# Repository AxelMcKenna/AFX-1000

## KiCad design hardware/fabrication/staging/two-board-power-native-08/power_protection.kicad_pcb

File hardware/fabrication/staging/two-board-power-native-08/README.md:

# TBP08: module-input branch and return-star candidate

The combined power schematic now includes a dedicated feed for both TMR 1-1215
modules and a separate primary force return through a copper net tie.
**This branch is not accepted for fabrication:** fault review identified a
post-short output-undervoltage condition that requires a different cutoff
strategy. The complete two-board unit remains unfinished.

Open [power_protection.kicad_pro](power_protection.kicad_pro).

| Native check | Result |
| --- | --- |
| Electrical parts / schematic pin entries | 1,090 / 3,413 |
| Footprints, including 15 mechanical | 1,105 |
| Physical pad instances mapped | 3,478 |
| Native geometry / schematic-parity findings | 0 / 0 |
| ERC | 0 errors; 2 retained floating-reference warnings |
| Open connections | **2,707** |
| Original parts / full footprint geometries preserved | 1,077 / 1,092 |

## Circuit captured

P_U101.17/.18 and P_C103.1 supply G_U1, a TPS259474LRPWR eFuse. Its output feeds
N_U17.2, N_U22.2 and the existing module input filters. This supply is available
before NF GLOBAL_MASTER; no final-enable dependency is introduced. The 13 new
parts comprise the eFuse, five resistors, four capacitors, two clamps and one
copper net tie. No physical part from TBP06 is removed or changed. The former
external-input power flag is removed because G_U1 now supplies that net.

G_NT1 joins PWR_MODULE_INPUT_GND to PWR_AGND. Its system-ground end must return
at P_C103.2. It is the only declared primary-return connection; there is no
local NF quiet-ground tie. The star currently sits near the bulk capacitor as
an **unrouted placement placeholder**. The new cell is also provisionally placed,
well away from its final electrically optimized location. Neither placement
establishes current-loop, ground-drop, thermal or housing acceptance.

The [independent audit](module-feed-audit.json) checks every new pin, preserves
the original complete pin partition and all 1,092 prior footprint geometries,
maps all physical pads, and rejects seven incorrect wiring variants. It also
rechecks the earlier 32 fault/reset cases, two source-sense channels and 64
settled UV-fault cases. The RPW footprint matches the reviewed manufacturer's
copper dimensions and stencil example; process acceptance remains open.

TBP07's first native check found nine new-cell spacing errors, three Datasheet
field mismatches and 46 schematic-grid warnings. TBP08 corrects those findings
without suppressing any check. [Native results](review.json) are independently
bound to the actual checked files.

## Electrical screens and unresolved fault

With a declared total resistance budget of 0.5% and the specified threshold and
input-leakage limits, the input branch enables at 10.466–11.111 V, disables on
falling input at 9.515–10.143 V and disables on rising input at 13.879–14.710 V.
These are conditional on the passive budget and local reference. The proposed
12 V ±5% supply window and 0.10 V branch-distribution allowance still need
acceptance against the complete supply and layout.

The nominal current limit is 0.514 A. Scaling the manufacturer's 6.65 kΩ test
row to the chosen 6.49 kΩ produces a 0.433–0.592 A **model screen**, not a new
guaranteed test row. The nominal output ramp is 28.2 ms to 12 V. A 0.35 A total
load and 60 µF total output capacitance fit a conditional charging-current
screen, but the modules' startup/internal capacitance and minimum efficiency
are not bounded by the available table. Exact passive order codes, effective
capacitance, surge behavior and per-module fault containment remain open.

Most importantly, the selected eFuse does not latch immediately on every short.
After fast trip it can restart in current limit. The audit records a hypothetical
12 V input / 8.7 V output case whose typical thermal model does not reach thermal
shutdown. Input undervoltage sensing cannot detect that output sag. This is an
identified protection gap, not evidence that a real unit was tested or failed.
The [cutoff review](../two-board-module-cutoff-review-01/README.md) identifies
TPS26601 in its timer-operated latch-off mode as the next candidate. It has not
yet replaced G_U1; its pin map, return reference, current/slew settings, land
pattern and circuit must be implemented and checked.

## Remaining work

Resolve the module cutoff and receiving limits, then complete loaded AUX,
reference/sense/clamp, high-temperature logic and deep-UV/minimum-OFF reviews.
Optimize critical power placement and route both boards; finish the signal/power
interface and ESS codec land pattern. Complete the manufacturing BOM/stack/
process and fabrication files, full installed-fit/support/cooling checks and
prototype inspection/bring-up plan. Prototype measurements belong in that plan;
they are not represented as measurements of an unbuilt unit.

The [native module-sheet SVG](plots-module/G_module_input.svg) was inspected.
Its long G_NT1 pin names overlap and should be shortened in the next circuit
revision. The hierarchy-cover export in `plots/schematic/` is not the module
sheet; the direct export linked here is the correct visual reference.

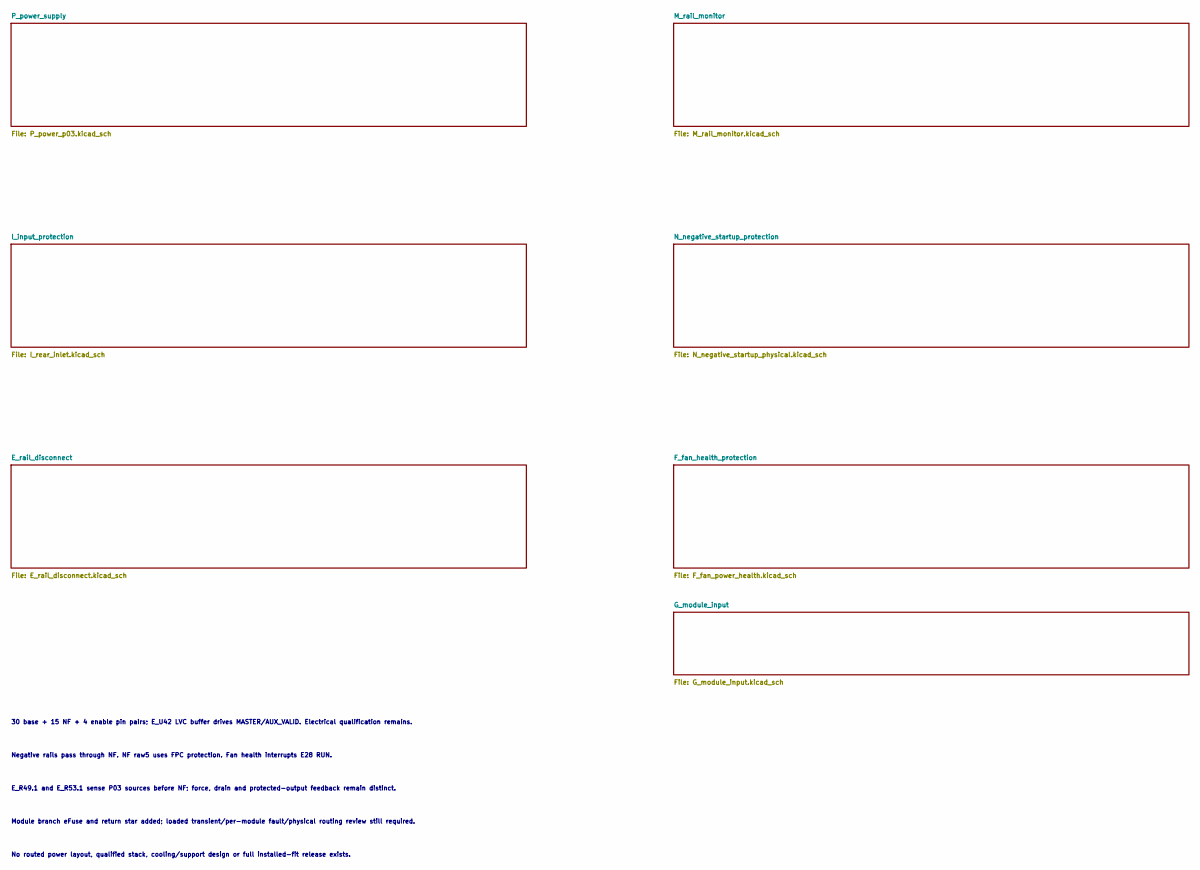
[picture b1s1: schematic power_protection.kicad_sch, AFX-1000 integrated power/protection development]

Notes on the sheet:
30 base + 15 NF + 4 enable pin pairs; E_U42 LVC buffer drives MASTER/AUX_VALID. Electrical qualification remains.
Negative rails pass through NF. NF raw5 uses FPC protection. Fan health interrupts E28 RUN.
E_R49.1 and E_R53.1 sense P03 sources before NF; force, drain and protected-output feedback remain distinct.
Module branch eFuse and return star added; loaded transient/per-module fault/physical routing review still required.
No routed power layout, qualified stack, cooling/support design or full installed-fit release exists.

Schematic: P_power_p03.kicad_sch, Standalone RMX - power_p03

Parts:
P_C1, P_C63: 10uF 63V X7R; C_1210_3225Metric
P_C2, P_C3, P_C5, P_C6, P_C8, P_C9, P_C37, P_C42, P_C52, P_C57, P_C64, P_C65, P_C67, P_C68, P_C70, P_C204, P_C205, P_C224, P_C225, P_C254: 22uF 50V X7R 20% TDK C3225X7R1H226M250AC; C_1210_3225Metric
P_C4, P_C7, P_C10, P_C35, P_C38, P_C40, P_C43, P_C50, P_C53, P_C55, P_C58, P_C59, P_C61, P_C66, P_C69, P_C71: 100nF 50V X7R; C_0805_2012Metric
P_C11, P_C30, P_C107, P_C108: 100nF 16V X7R; C_0805_2012Metric
P_C12, P_C14, P_C73, P_C75: 68pF 50V C0G 5%; C_0805_2012Metric
P_C13, P_C15, P_C74, P_C76: 330nF 16V X7R; C_0805_2012Metric
P_C31: 2.2uF 16V X7R; C_0805_2012Metric
P_C32, P_C33: 1uF film 63V 10% MKS2C041001F00KSSD; C_Rect_L7.2mm_W5.0mm_P5.00mm
P_C34, P_C39, P_C49, P_C54, P_C240: 47nF 50V C0G 5%; C_1210_3225Metric
P_C36, P_C41, P_C51, P_C56: 10uF 50V X7R; C_1210_3225Metric
P_C60, P_C62, P_C105: 1uF 50V X7R; C_0805_2012Metric
P_C72, P_C210, P_C211, P_C230, P_C231: 100nF 50V X7R 10% TDK C1005X7R1H104K050BB; C_0402_1005Metric
P_C101, P_C102: 2.2uF 100V X7R; C_1210_3225Metric
P_C103: 220uF 35V electrolytic 20% (EEUFR1V221); CP_Radial_D8.0mm_P3.50mm
P_C104: 1uF 50V X7R; C_1210_3225Metric
P_C106: 10uF 25V X7R 10% TDK C3225X7R1E106K250AC; C_1210_3225Metric
P_C109: 1nF 16V C0G 5%; C_0805_2012Metric
P_C110: 10nF 25V C0G 5% KEMET C0603C103J3GACTU; C_0603_1608Metric
P_C113: 1uF 100V X7S 10% TDK C2012X7S2A105K125AE; C_0805_2012Metric
P_C200, P_C220: 4.7uF 25V X7R 10% TDK C2012X7R1E475K125AB; C_0805_2012Metric
P_C201, P_C221, P_C255, P_C301, P_C302: 100nF 50V X7R; C_0603_1608Metric
P_C202, P_C203, P_C222, P_C223: 2.2uF 50V X7R 10% TDK C2012X7R1H225K125AC; C_0805_2012Metric
P_C206, P_C207, P_C208, P_C209, P_C226, P_C227, P_C228, P_C229: 47uF 25V X7S 20% TDK C3225X7S1E476M250AC; C_1210_3225Metric
P_C241: 1uF 25V X7R; C_1210_3225Metric
P_C242, P_C243, P_C244, P_C245, P_C246, P_C247, P_C248, P_C249, P_C250, P_C251: 100nF 25V C0G 5% KEMET C1206C104J3GACTU; C_1206_3216Metric
P_C252, P_C253: 1uF 16V X7R; C_1210_3225Metric
P_C300: 10nF 50V C0G 5%; C_0805_2012Metric
P_C401, P_C402: 100nF 50V X7R C0603C104K5RACTU; C0603
P_C403: 10nF 50V C0G C0603C103J5GACTU; C0603
P_D1, P_D2, P_D3, P_D4, P_D103: SS16-E3/61T; D_SMA
P_D101: SMBJ33CA-E3/52; D_SMB
P_D102: BAS116,215; SOT-23
P_J2: Header6; PinHeader_1x06_P2.54mm_Vertical
P_J3: Header2; PinHeader_1x02_P2.54mm_Vertical
P_J20, P_J21, P_J23, P_J24: Wurth 7466003R M3 SMT; Wurth_7466003R
P_J22: P03 READY test; PinHeader_1x03_P2.54mm_Vertical
P_J103: Bare POWER_READY probe pads, no fitted header; Probe2_P2.54_D1
P_J104: JST B3B-XH-A (XHP-3/SXH-001T-P0.6); JST_XH_B3B-XH-A_1x03_P2.50mm_Vertical
P_J106: JST B4B-XH-A (XHP-4/SXH-001T-P0.6); JST_XH_B4B-XH-A_1x04_P2.50mm_Vertical
P_L1, P_L6: 33uH 20% SRP7050WA-330M; SRP7050WA
P_L2, P_L3, P_L7, P_L8: 68uH 20% SRP1050WA-680M; SRP1050WA
P_L20, P_L23: 4.7uH 20% Coilcraft XAL7030-472MEC; L_Coilcraft_XAL7030-472
P_Q101: PSMN012-100YL,115; LFPAK56
P_Q102: BSS138-7-F; SOT-23
P_Q103: DMN2056U-7; SOT-23
P_R1: 300k 0.01% 5ppm; R_0805_2012Metric
P_R2, P_R3, P_R4, P_R45, P_R46: 15k 0.01% 5ppm; R_0805_2012Metric
P_R5, P_R20, P_R21, P_R34, P_R35: 330k 0.01% 5ppm; R_0805_2012Metric
P_R6, P_R7, P_R49, P_R50: 4.7k 1%; R_0805_2012Metric
P_R17, P_R19, P_R110: 1k 1%; R_0805_2012Metric
P_R18, P_R120: 100k 1%; R_0805_2012Metric
P_R22, P_R27, P_R36, P_R41, P_R243, P_R244: 100k 0.01% 5ppm; R_0805_2012Metric
P_R23, P_R28, P_R37, P_R42, P_R241: 6.8k 1%; R_0805_2012Metric
P_R24, P_R38: 9.09k 1%; R_0805_2012Metric
P_R25, P_R39, P_R47, P_R306: 200k 0.01% 5ppm; R_0805_2012Metric
P_R26, P_R40, P_R308: 180k 0.01% 5ppm; R_0805_2012Metric
P_R29, P_R43: 5.62k 1%; R_0805_2012Metric
P_R44: 240k 0.01% 5ppm; R_0805_2012Metric
P_R48, P_R301, P_R303, P_R305, P_R307, P_R309, P_R314: 10k 0.01% 5ppm; R_0805_2012Metric
P_R101, P_R103, P_R117: 309k 0.1% 10ppm; R_0805_2012Metric
P_R102: 40.2k 0.1% 10ppm; R_0805_2012Metric
P_R104: 28k 0.1% 10ppm; R_0805_2012Metric
P_R105: 68.1k 0.1% 10ppm; R_0805_2012Metric
P_R106, P_R109, P_R118, P_R119: 10k 0.1% 10ppm; R_0805_2012Metric
P_R107: 4.02k 0.1% 10ppm; R_0805_2012Metric
P_R108: 11.7k 0.1% 10ppm; R_0805_2012Metric
P_R111, P_R204, P_R224, P_R246: 10k 1%; R_0805_2012Metric
P_R112, P_R114: 47k 1%; R_0805_2012Metric
P_R113: 3.3k 1%; R_0805_2012Metric
P_R115: 30.9k 0.1% 10ppm; R_0805_2012Metric
P_R116: 3.09k 0.1% 10ppm; R_0805_2012Metric
P_R121: 100 1%; R_0805_2012Metric
P_R130: 49.9 0.01% 5ppm; R_0805_2012Metric
P_R200: 9k 0.01% 2ppm Susumu RG2012L-902-L-T1; R_0805_2012Metric
P_R201: 1k 0.01% 2ppm Susumu RG2012L-102-L-T1; R_0805_2012Metric
P_R202, P_R222: 24.3k 1%; R_0805_2012Metric
P_R203, P_R223: 18.2k 0.1% 25ppm Panasonic ERA6AEB1822V; R_0805_2012Metric
P_R205, P_R225: 22k 1%; R_0805_2012Metric
P_R206: 54.9 0.1% 25ppm Panasonic ERA6AEB549V; R_0805_2012Metric
P_R220: 11k 0.01% 5ppm; R_0805_2012Metric
P_R221, P_R311: 1k 0.01% 5ppm; R_0805_2012Metric
P_R240: 100 0.01% 5ppm; R_0805_2012Metric
P_R242: 120 0.01% 5ppm; R_0805_2012Metric
P_R245: 2.21k 1%; R_0805_2012Metric
P_R300, P_R302: 87.6k 0.01% 5ppm; R_0805_2012Metric
P_R304: 324k 0.01% 5ppm; R_0805_2012Metric
P_R310: 590 0.01% 5ppm; R_0805_2012Metric
P_R312: 7.5k 0.01% 5ppm; R_0805_2012Metric
P_R313: 1M 0.01% 5ppm; R_0805_2012Metric
P_R315: 750k 0.01% 5ppm; R_0805_2012Metric
P_R316: 2.2k 0.1% 25ppm Panasonic ERA6AEB222V; R_0805_2012Metric
P_R401: 100k ohm TNPW0805100KBEEA; R0805
P_R402: 10M 1% CRCW080510M0FKEA; R0805
P_R403: 1k 1% CRCW12061K00FKEA; R1206
P_U1, P_U13: LT3471EDD#PBF; DFN-10-1EP_3x3mm_P0.5mm_EP1.65x2.38mm
P_U4: REF5025EIDR; SOIC-8_3.9x4.9mm_P1.27mm
P_U5: OPA4192ID; SOIC-14_3.9x8.7mm_P1.27mm
P_U6, P_U24: OPA2192ID; SOIC-8_3.9x4.9mm_P1.27mm
P_U7: LT3080IMS8E#PBF; MSOP-8-1EP_3x3mm_P0.65mm_EP1.68x1.88mm
P_U8: LT3080IQ#PBF; TO-263-5_TabPin3
P_U10, P_U11: LT3090IDD#PBF; DFN-10-1EP_3x3mm_P0.5mm_EP1.65x2.38mm
P_U12: LT1634AIS8-2.5#PBF; SOIC-8_3.9x4.9mm_P1.27mm
P_U20, P_U23: TPS543620RPYR; TPS543620_RPY0014A
P_U21: ADR4550BRZ; SOIC-8_3.9x4.9mm_P1.27mm
P_U22: LT3045IDD#PBF; DFN-10-1EP_3x3mm_P0.5mm_EP1.65x2.38mm
P_U25: LTC2910HGN#PBF; SSOP-16_3.9x4.9mm_P0.635mm
P_U26: SN74LVC1G97DBVR; SOT-23-6
P_U101: TPS26630RGER; Texas_RGE0024H_VQFN-24-1EP_4x4mm_P0.5mm_EP2.7x2.7mm
P_U102: TPS7A1601DGNR; MSOP-8-1EP_3x3mm_P0.65mm_EP1.68x1.88mm
P_U103: TLV7011DBVR; SOT-23-5
P_U201: TPS389001DSET; TI_DSE0006A
P_U202: SN74AUP1G17DCKR; TI_DCK0005A

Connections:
/P_power_supply/AUX_FB: P_R109.1, P_R130.2, P_U102.2 (FB)
/P_power_supply/AUX_START_DELAY: P_C110.1 (+), P_U102.7 (DELAY)
/P_power_supply/AX03_RUN_DRIVE: P_R403.1, P_U202.4 (Y)
/P_power_supply/AX03_SOURCE_CT: P_C403.1, P_U201.5 (CT)
/P_power_supply/AX03_SOURCE_RESET: P_R401.2, P_R402.1, P_U201.6 (RESET_N), P_U202.2 (A)
/P_power_supply/BLOCK_DRV: P_Q102.1 (GATE), P_U101.4 (DRV)
/P_power_supply/BLOCK_GATE: P_Q101.4 (GATE), P_Q102.3 (DRAIN), P_U101.3 (B_GATE)
/P_power_supply/CUK_NODE: P_C1.2, P_D2.2 (A), P_L3.1
/P_power_supply/FAST_OV_GATE: P_Q103.1 (GATE), P_R120.1, P_R121.2
/P_power_supply/FAST_OV_OUT: P_R117.1, P_R121.1, P_U103.1 (OUT)
/P_power_supply/FAST_OV_REF: P_C109.1 (+), P_R118.2, P_R119.1, P_U103.4 (IN-)
/P_power_supply/FAST_OV_SENSE: P_R115.2, P_R116.1, P_R117.2, P_U103.3 (IN+)
/P_power_supply/INPUT_ILIM: P_R107.1, P_U101.10 (ILIM)
/P_power_supply/INPUT_OV: P_D102.1 (ANODE), P_R103.2, P_R104.1, P_U101.7 (OVP)
/P_power_supply/INPUT_PGTH: P_R105.2, P_R106.1, P_U101.15 (PGTH)
/P_power_supply/INPUT_SLEW: P_C105.1 (+), P_U101.9 (dVdT)
/P_power_supply/INPUT_UV: P_R101.2, P_R102.1, P_U101.6 (UVLO)
/P_power_supply/LO_CUK_NODE: P_C63.2, P_D4.2 (A), P_L8.1
/P_power_supply/LO_N_FB: P_C75.2, P_R46.2, P_R47.1, P_U13.4 (FB2P)
/P_power_supply/LO_N_RMID: P_R47.2, P_R48.1
/P_power_supply/LO_N_SS: P_C76.1, P_R50.2, P_U13.7 (SHDN_SS2)
/P_power_supply/LO_N_SW: P_C63.1, P_L7.2, P_U13.6 (SW2)
/P_power_supply/LO_P_FB: P_C73.2, P_R44.2, P_R45.1, P_U13.1 (FB1N)
/P_power_supply/LO_P_SS: P_C74.1, P_R49.2, P_U13.9 (SHDN_SS1)
/P_power_supply/LO_P_SW: P_D3.2 (A), P_L6.2, P_U13.10 (SW1)
/P_power_supply/LO_REF_1V: P_C72.1, P_R46.1, P_U13.2 (FB1P), P_U13.3 (VREF)
/P_power_supply/N12_DRIVE: P_C54.1, P_R42.1, P_U6.7 (OUT)
/P_power_supply/N12_FB: P_C54.2, P_R40.2, P_R41.1, P_U6.6 (-)
/P_power_supply/N12_RMID: P_R39.2, P_R40.1
/P_power_supply/N12_SET: P_C55.1, P_R39.1, P_R42.2, P_U11.4 (SET)
/P_power_supply/N19_DRIVE: P_C49.1, P_R37.1, P_U6.1 (OUT)
/P_power_supply/N19_FB: P_C49.2, P_R35.2, P_R36.1, P_U6.2 (-)
/P_power_supply/N19_RMID: P_R34.2, P_R35.1
/P_power_supply/N19_SET: P_C50.1, P_R34.1, P_R37.2, P_U10.4 (SET)
/P_power_supply/NREF_2V5: P_R18.1, P_R19.1, P_U12.4 (GND/ANODE), P_U12.5 (TEST)
/P_power_supply/NREF_FILTER: P_C33.1, P_R19.2, P_U6.3 (+), P_U6.5 (+)
/P_power_supply/P03_ANA_DIV: P_R242.2, P_R243.1, P_R244.1
/P_power_supply/P03_ANA_DRIVE: P_C240.1 (+), P_R241.1, P_U24.1 (OUT_A)
/P_power_supply/P03_ANA_FB: P_C240.2 (-), P_R244.2, P_U24.2 (IN_A_N)
/P_power_supply/P03_ANA_SET: P_C241.1 (+), P_R241.2, P_R242.1, P_U22.7 (SET)
/P_power_supply/P03_AUX_TRIM: P_R108.2, P_R130.1
/P_power_supply/P03_A_BOOT: P_C221.1 (+), P_U23.14 (BOOT)
/P_power_supply/P03_A_BP5: P_C220.1 (+), P_U23.6 (BP5)
/P_power_supply/P03_A_ENABLE: P_R224.2, P_R225.1, P_U23.7 (EN)
/P_power_supply/P03_A_FB: P_R220.2, P_R221.1, P_U23.4 (FB)
/P_power_supply/P03_A_FSEL: P_R222.1, P_U23.1 (SYNC_FSEL)
/P_power_supply/P03_A_MODE: P_R223.1, P_U23.2 (MODE)
/P_power_supply/P03_A_SW: P_C221.2 (-), P_L23.1 (SW), P_U23.10 (SW), P_U23.13 (SW_BOOT_RETURN)
/P_power_supply/P03_D_BOOT: P_C201.1 (+), P_U20.14 (BOOT)
/P_power_supply/P03_D_BP5: P_C200.1 (+), P_U20.6 (BP5)
/P_power_supply/P03_D_ENABLE: P_R204.2, P_R205.1, P_U20.7 (EN)
/P_power_supply/P03_D_FB: P_R201.1, P_R206.2, P_U20.4 (FB)
/P_power_supply/P03_D_FB_TRIM: P_R200.2, P_R206.1
/P_power_supply/P03_D_FSEL: P_R202.1, P_U20.1 (SYNC_FSEL)
/P_power_supply/P03_D_MODE: P_R203.1, P_U20.2 (MODE)
/P_power_supply/P03_D_SW: P_C201.2 (-), P_L20.1 (SW), P_U20.10 (SW), P_U20.13 (SW_BOOT_RETURN)
/P_power_supply/P03_MON_ANA: P_R302.2, P_R303.1, P_U25.2 (V2)
/P_power_supply/P03_MON_BUCK_OK: P_U25.5 (V5), P_U26.4 (Y)
/P_power_supply/P03_MON_DIG: P_R300.2, P_R301.1, P_U25.1 (V1)
/P_power_supply/P03_MON_N12: P_R314.2, P_R315.1, P_U25.8 (V8)
/P_power_supply/P03_MON_N19: P_R312.2, P_R313.1, P_U25.7 (V7)
/P_power_supply/P03_MON_NEG_BIAS: P_R310.2, P_R311.1, P_R312.1, P_R314.1
/P_power_supply/P03_MON_P12: P_R306.2, P_R307.1, P_U25.4 (V4)
/P_power_supply/P03_MON_P19: P_R304.2, P_R305.1, P_U25.3 (V3)
/P_power_supply/P03_MON_REF: P_R310.1, P_U25.10 (REF)
/P_power_supply/P03_MON_TIMER: P_C300.1 (+), P_U25.15 (TMR)
/P_power_supply/P03_MON_VIN: P_R308.2, P_R309.1, P_U25.6 (V6)
/P_power_supply/P03_PRE6V: P_C226.1 (+), P_C227.1 (+), P_C228.1 (+), P_C229.1 (+), P_C253.1 (+), P_L23.2 (OUT), P_R220.1, P_U21.2 (VIN), P_U22.1 (IN), P_U22.2 (IN), P_U22.3 (EN_UV), P_U22.6 (PGFB)
/P_power_supply/P03_REF5: P_C252.1 (+), P_R240.1, P_U21.6 (VOUT)
/P_power_supply/P03_REF_FILTER: P_C242.1 (+), P_C243.1 (+), P_C244.1 (+), P_C245.1 (+), P_C246.1 (+), P_C247.1 (+), P_C248.1 (+), P_C249.1 (+), P_C250.1 (+), P_C251.1 (+), P_R240.2, P_U24.3 (IN_A_P)
/P_power_supply/P03_SOURCES_READY: P_R246.2, P_U20.3 (PGOOD), P_U23.3 (PGOOD), P_U26.3 (In0)
/P_power_supply/P03_SPARE_24: P_U24.6 (IN_B_N), P_U24.7 (OUT_B)
/P_power_supply/P03_SPARE_C: P_U5.8 (OUT), P_U5.9 (-)
/P_power_supply/P12_DRIVE: P_C39.1, P_R28.1, P_U5.7 (OUT)
/P_power_supply/P12_FB: P_C39.2, P_R26.2, P_R27.1, P_U5.6 (-)
/P_power_supply/P12_RMID: P_R25.2, P_R26.1
/P_power_supply/P12_SET: P_C40.1, P_R25.1, P_R28.2, P_U8.2 (SET)
/P_power_supply/P19_DRIVE: P_C34.1, P_R23.1, P_U5.1 (OUT)
/P_power_supply/P19_FB: P_C34.2, P_R21.2, P_R22.1, P_U5.2 (-)
/P_power_supply/P19_RMID: P_R20.2, P_R21.1
/P_power_supply/P19_SET: P_C35.1, P_R20.1, P_R23.2, P_U7.4 (SET)
/P_power_supply/POWER_READY: P_J22.3 (POWER_READY), P_J103.2 (POWER_READY), P_R110.2, P_R204.1, P_R224.1, P_U26.6 (In2), P_U101.16 (PGOOD)
/P_power_supply/PREF_2V5: P_C31.1, P_R17.1, P_U4.6 (VOUT)
/P_power_supply/PREF_FILTER: P_C32.1, P_R17.2, P_U5.3 (+), P_U5.5 (+)
/P_power_supply/RAW_N17: P_C56.1, P_C67.1, P_C68.1, P_C69.1, P_C75.1, P_L8.2, P_R48.2, P_U11.8 (ILIM), P_U11.9 (IN), P_U11.10 (IN), P_U11.11 (EP/IN)
/P_power_supply/RAW_N22: P_C8.1, P_C9.1, P_C10.1, P_C14.1, P_C51.1, P_C61.1, P_C62.1, P_L3.2, P_R5.2, P_R18.2, P_U6.4 (V-), P_U10.8 (ILIM), P_U10.9 (IN), P_U10.10 (IN), P_U10.11 (EP/IN)
/P_power_supply/RAW_N_FB: P_C14.2, P_R4.2, P_R5.1, P_U1.4 (FB2P)
/P_power_supply/RAW_N_SS: P_C15.1, P_R7.2, P_U1.7 (SHDN_SS2)
/P_power_supply/RAW_N_SW: P_C1.1, P_L2.2, P_U1.6 (SW2)
/P_power_supply/RAW_P17: P_C41.1, P_C64.1, P_C65.1, P_C66.1, P_C73.1, P_D3.1 (K), P_R44.1, P_U8.4 (VCONTROL), P_U8.5 (IN)
/P_power_supply/RAW_P22: P_C5.1, P_C6.1, P_C7.1, P_C12.1, P_C36.1, P_C59.1, P_C60.1, P_D1.1 (K), P_R1.1, P_U5.4 (V+), P_U7.5 (VCONTROL), P_U7.7 (IN), P_U7.8 (IN)
/P_power_supply/RAW_P_FB: P_C12.2, P_R2.2, P_R3.1, P_U1.1 (FB1N)
/P_power_supply/RAW_P_RMID: P_R1.2, P_R2.1
/P_power_supply/RAW_P_SS: P_C13.1, P_R6.2, P_U1.9 (SHDN_SS1)
/P_power_supply/RAW_P_SW: P_D1.2 (A), P_L1.2, P_U1.10 (SW1)
/P_power_supply/SPARE_OUT: P_U5.13 (SPARE-), P_U5.14 (SPARE_OUT)
/P_power_supply/SW_REF_1V: P_C11.1, P_R4.1, P_U1.2 (FB1P), P_U1.3 (VREF)
/P_power_supply/VIN_IC: P_C102.1 (+), P_C113.1 (+), P_Q101.5 (DRAIN/MB), P_R115.1, P_U101.1 (IN), P_U101.2 (IN), P_U102.5 (EN), P_U102.8 (IN)
PWR_5V_DIG_SRC: P_C30.1, P_C206.1 (+), P_C207.1 (+), P_C208.1 (+), P_C209.1 (+), P_J3.1 (5V_DIG), P_J23.1, P_L20.2 (OUT), P_R6.1, P_R7.1, P_R49.1, P_R50.1, P_R200.1, P_R300.1, P_U4.1 (EN), P_U4.2 (VIN), P_U10.5 (SHDN), P_U11.5 (SHDN); also elsewhere on the board
PWR_AGND: P_C2.2, P_C3.2, P_C4.2, P_C5.2, P_C6.2, P_C7.2, P_C8.2, P_C9.2, P_C10.2, P_C11.2, P_C13.2, P_C15.2, P_C30.2, P_C31.2, P_C32.2, P_C33.2, P_C35.2, P_C36.2, P_C37.2, P_C38.2, P_C40.2, P_C41.2, P_C42.2, P_C43.2, P_C50.2, P_C51.2, P_C52.2, P_C53.2, P_C55.2, P_C56.2, P_C57.2, P_C58.2, P_C59.2, P_C60.2, P_C61.2, P_C62.2, P_C64.2, P_C65.2, P_C66.2, P_C67.2, P_C68.2, P_C69.2, P_C70.2, P_C71.2, P_C72.2, P_C74.2, P_C76.2, P_C101.2 (-), P_C102.2 (-), P_C103.2 (-), P_C104.2 (-), P_C105.2 (-), P_C106.2 (-), P_C107.2 (-), P_C108.2 (-), P_C109.2 (-), P_C110.2 (-), P_C113.2 (-), P_C200.2 (-), P_C202.2 (-), P_C203.2 (-), P_C204.2 (-), P_C205.2 (-), P_C206.2 (-), P_C207.2 (-), P_C208.2 (-), P_C209.2 (-), P_C210.2 (-), P_C211.2 (-), P_C220.2 (-), P_C222.2 (-), P_C223.2 (-), P_C224.2 (-), P_C225.2 (-), P_C226.2 (-), P_C227.2 (-), P_C228.2 (-), P_C229.2 (-), P_C230.2 (-), P_C231.2 (-), P_C241.2 (-), P_C242.2 (-), P_C243.2 (-), P_C244.2 (-), P_C245.2 (-), P_C246.2 (-), P_C247.2 (-), P_C248.2 (-), P_C249.2 (-), P_C250.2 (-), P_C251.2 (-), P_C252.2 (-), P_C253.2 (-), P_C254.2 (-), P_C255.2 (-), P_C300.2 (-), P_C301.2 (-), P_C302.2 (-), P_C401.2, P_C402.2, P_C403.2, P_D2.1 (K), P_D4.1 (K), P_D101.2, P_D103.2 (ANODE), P_J2.2 (AGND), P_J3.2 (AGND), P_J20.1, P_J21.1, P_J22.2 (AGND), P_J103.1 (AGND), P_J104.3 (AGND), P_J106.2 (AGND), P_Q103.2 (SOURCE), P_R3.2, P_R22.2, P_R24.2, P_R27.2, P_R29.2, P_R36.2, P_R38.2, P_R41.2, P_R43.2, P_R45.2, P_R102.2, P_R104.2, P_R106.2, P_R107.2, P_R109.2, P_R111.2, P_R112.2, P_R114.2, P_R116.2, P_R119.2, P_R120.2, P_R201.2, P_R202.2, P_R203.2, P_R205.2, P_R221.2, P_R222.2, P_R223.2, P_R225.2, P_R243.2, P_R245.2, P_R301.2, P_R303.2, P_R305.2, P_R307.2, P_R309.2, P_R311.2, P_R402.2, P_U1.5 (FB2N), P_U1.11 (GND_EP), P_U4.4 (GND), P_U5.10 (+), P_U5.11 (V-), P_U5.12 (SPARE+), P_U6.8 (V+), P_U10.3 (GND), P_U11.3 (GND), P_U12.6 (VOUT/CATHODE), P_U13.5 (FB2N), P_U13.11 (GND_EP), P_U20.5 (AGND), P_U20.9 (PGND), P_U20.11 (PGND), P_U21.4 (GND), P_U22.5 (ILIM), P_U22.8 (GND), P_U22.11 (EP_GND), P_U23.5 (AGND), P_U23.9 (PGND), P_U23.11 (PGND), P_U24.4 (V_N), P_U24.5 (IN_B_P), P_U25.9 (GND), P_U25.13 (DIS), P_U25.14 (SEL), P_U26.1 (In1_AND_CONFIG_LOW), P_U26.2 (GND), P_U101.8 (GND), P_U101.25 (EP/GND), P_U102.4 (GND), P_U102.9 (EP/GND), P_U103.2 (VEE), P_U201.2 (GND), P_U202.3 (GND); also elsewhere on the board
PWR_DC_IN: P_C101.1 (+), P_D101.1, P_Q101.1 (SOURCE), P_Q101.2 (SOURCE), P_Q101.3 (SOURCE), P_Q102.2 (SOURCE), P_R101.1, P_R103.1, P_U101.5 (IN_SYS); also elsewhere on the board
PWR_N12_SOURCE: P_C57.1, P_C58.1, P_J2.5 (N12), P_R43.1, P_R315.2, P_U11.1 (OUT), P_U11.2 (OUT); also elsewhere on the board
PWR_N19_SOURCE: P_C52.1, P_C53.1, P_J2.3 (N19), P_R38.1, P_R313.2, P_U10.1 (OUT), P_U10.2 (OUT); also elsewhere on the board
PWR_P03_SOURCES_READY: P_J22.1 (ALL_SOURCES_READY), P_J106.4 (SOURCE_READY), P_R316.2, P_U25.12 (RST_ACTIVE_LOW); also elsewhere on the board
PWR_P12_SRC: P_C42.1, P_C43.1, P_J2.4 (P12), P_R29.1, P_R306.1, P_U8.3 (OUT/TAB); also elsewhere on the board
PWR_P19_SRC: P_C37.1, P_C38.1, P_J2.1 (P19), P_R24.1, P_R304.1, P_U7.1 (OUT), P_U7.2 (OUT), P_U7.3 (OUT), P_U7.9 (EP/OUT); also elsewhere on the board
PWR_POWER_RUN: P_J104.2 (POWER_RUN), P_Q103.3 (DRAIN), P_R112.1, P_U101.12 (SHDN), P_U102.3 (PG), P_U201.1 (SENSE); also elsewhere on the board
PWR_RUN_BEFORE_FAN: P_J106.3 (POWER_RUN), P_R403.2; also elsewhere on the board
PWR_SWITCH_SUPPLY: P_J104.1 (SWITCH_SUPPLY), P_R113.2; also elsewhere on the board
PWR_V2V5_AUX: P_C106.1 (+), P_C107.1 (+), P_C108.1 (+), P_C301.1 (+), P_C302.1 (+), P_C401.1, P_C402.1, P_D102.3 (CATHODE), P_J106.1 (V2V5_AUX), P_R108.1, P_R110.1, P_R111.1, P_R113.1, P_R118.1, P_R246.1, P_R316.1, P_R401.1, P_U25.16 (VCC), P_U26.5 (VCC), P_U102.1 (OUT), P_U103.5 (VCC), P_U201.3 (MR), P_U201.4 (VDD), P_U202.5 (VCC); also elsewhere on the board
PWR_V5_REG_SRC: P_C254.1 (+), P_J2.6 (V5_REG), P_J24.1, P_R245.1, P_R302.1, P_U22.9 (OUTS), P_U22.10 (OUT); also elsewhere on the board

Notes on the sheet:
AX03 prototype: only J106.3 buffered; internal POWER_RUN, R113 and PG topology retained. No physical/fabrication release.

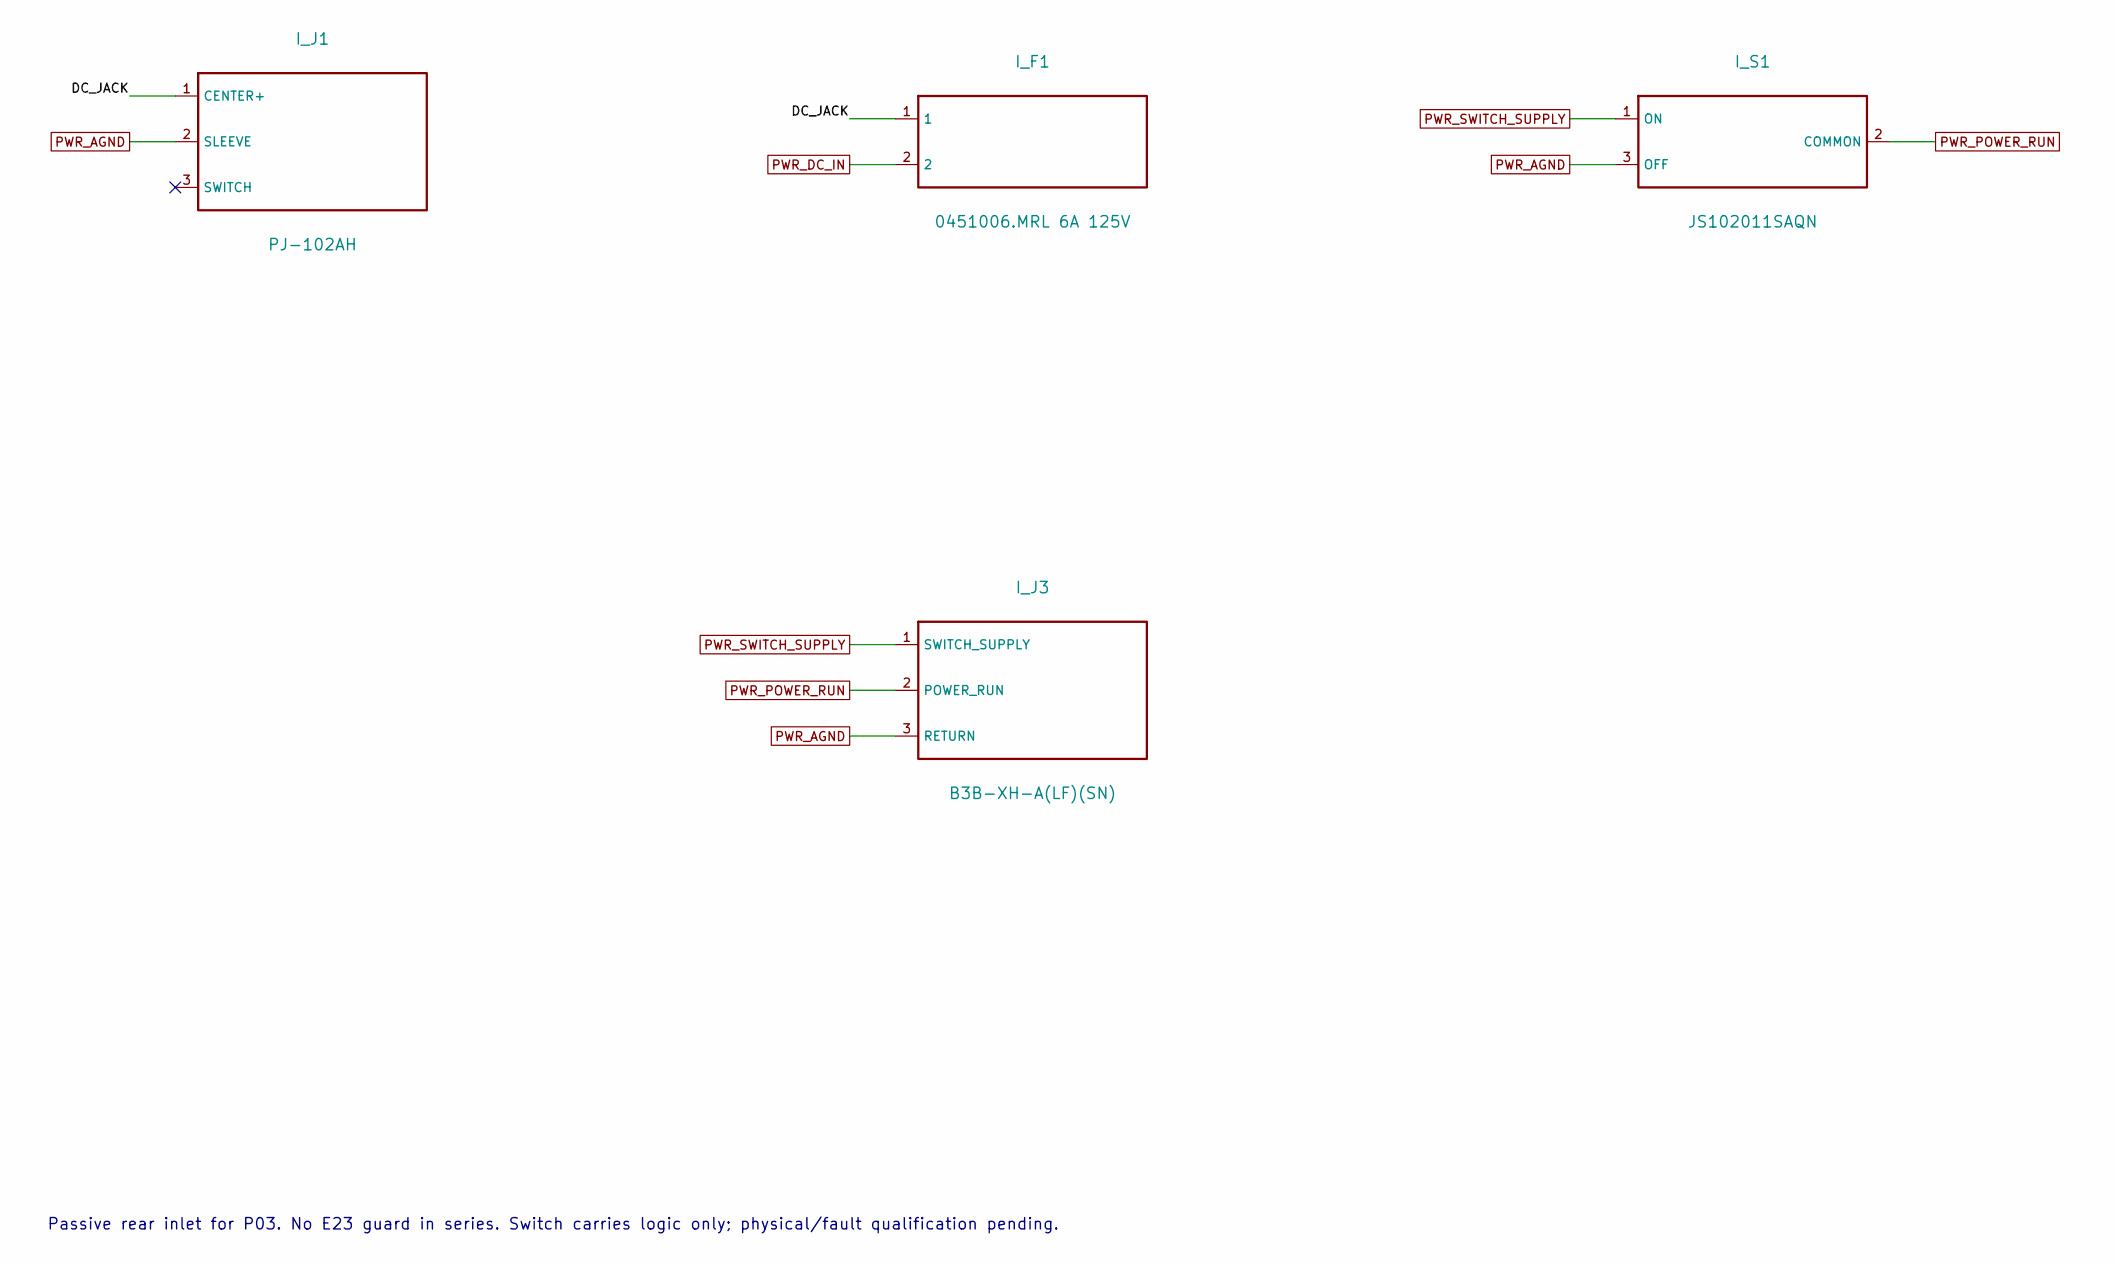
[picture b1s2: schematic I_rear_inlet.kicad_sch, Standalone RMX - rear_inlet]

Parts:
I_F1: 0451006.MRL 6A 125V; Fuse_Littelfuse-NANO2-451_453
I_J1: PJ-102AH; PJ102AH_RearEdge_E23
I_J3: B3B-XH-A(LF)(SN); JST_XH_B3B-XH-A_1x03_P2.50mm_Vertical
I_S1: JS102011SAQN; JS102011SAQN_RearEdge_E23

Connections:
/I_input_protection/DC_JACK: I_F1.1, I_J1.1 (CENTER+)
PWR_AGND: I_J1.2 (SLEEVE), I_J3.3 (RETURN), I_S1.3 (OFF); also elsewhere on the board
PWR_DC_IN: I_F1.2; also elsewhere on the board
PWR_POWER_RUN: I_J3.2 (POWER_RUN), I_S1.2 (COMMON); also elsewhere on the board
PWR_SWITCH_SUPPLY: I_J3.1 (SWITCH_SUPPLY), I_S1.1 (ON); also elsewhere on the board

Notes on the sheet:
Passive rear inlet for P03. No E23 guard in series. Switch carries logic only; physical/fault qualification pending.
